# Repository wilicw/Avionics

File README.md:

# Avionics System

## Get Started

### [Install PlatformIO CLI](https://docs.platformio.org/en/latest/)

### Build Source Code

```
make
```

### Upload

```
make upload
```

## System Architecture

## [LICENSE](https://github.com/NCKU-ISP/Avionics/blob/main/LICENSE)

## Contact Us

To report any bugs or commit any new features, please create a new pull request and describe the issues in detail. If you are interested in our project and want to support us, please contact us with the following email: e94066157@gs.ncku.edu.tw, thanks!

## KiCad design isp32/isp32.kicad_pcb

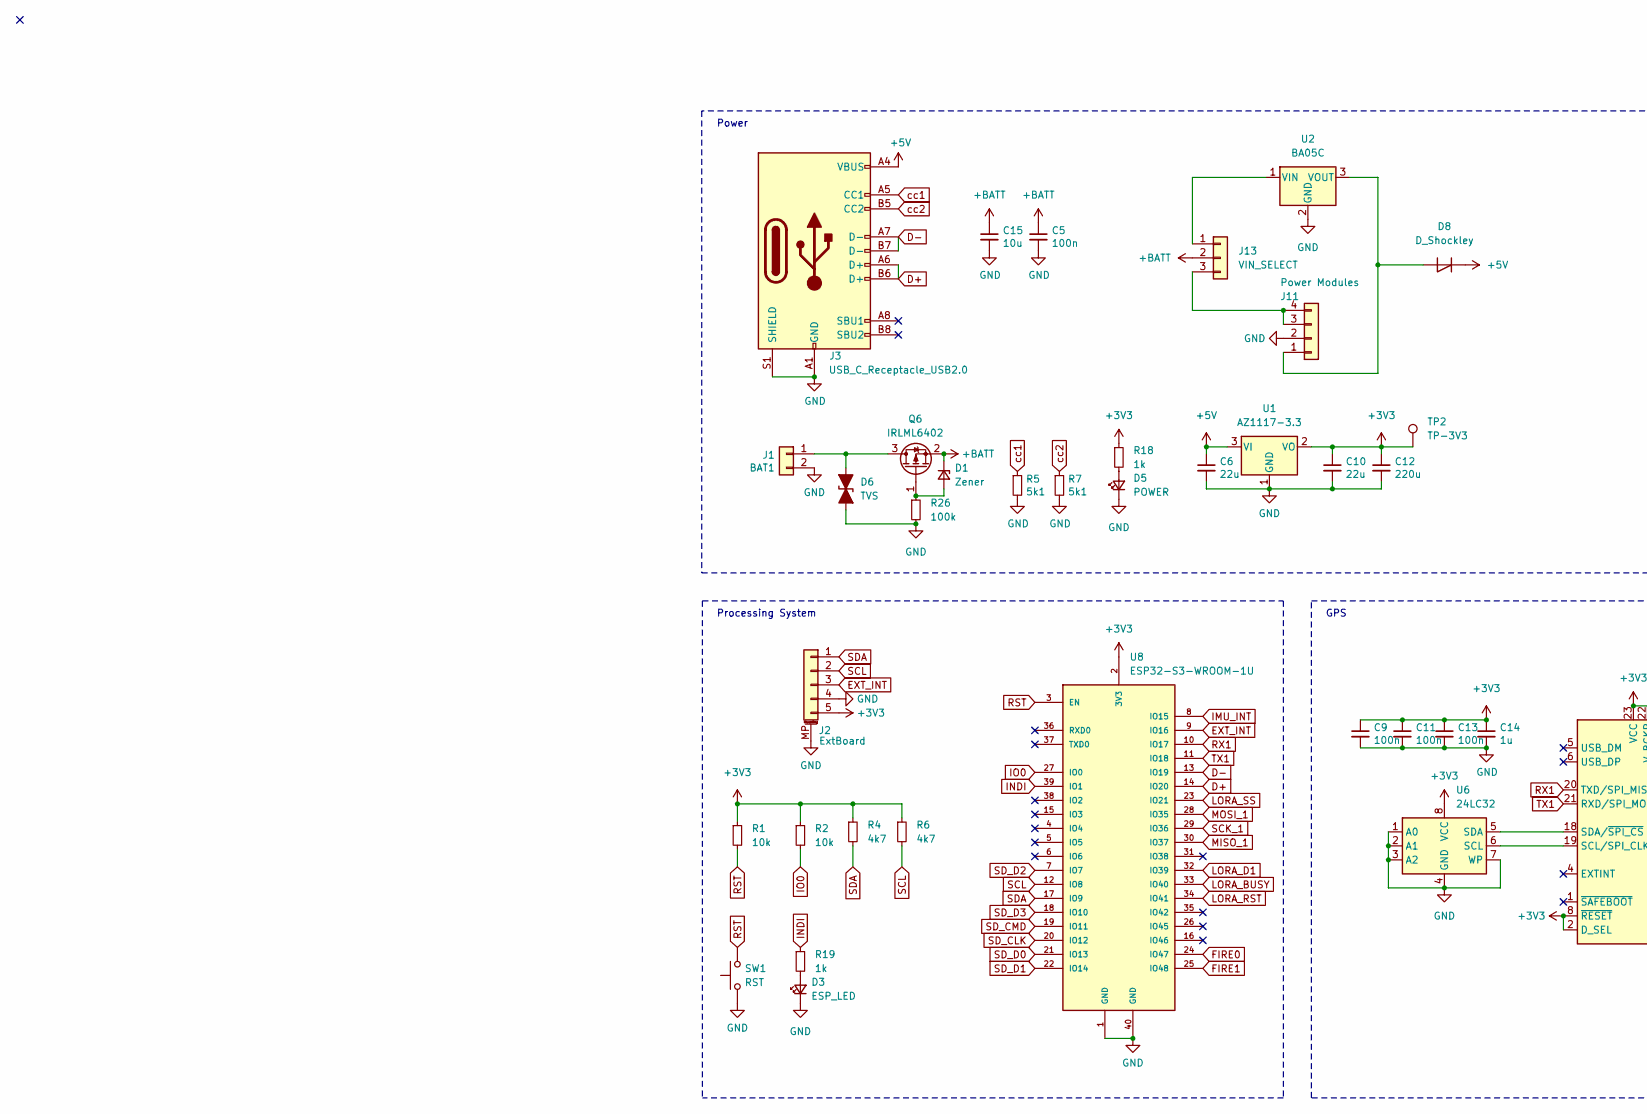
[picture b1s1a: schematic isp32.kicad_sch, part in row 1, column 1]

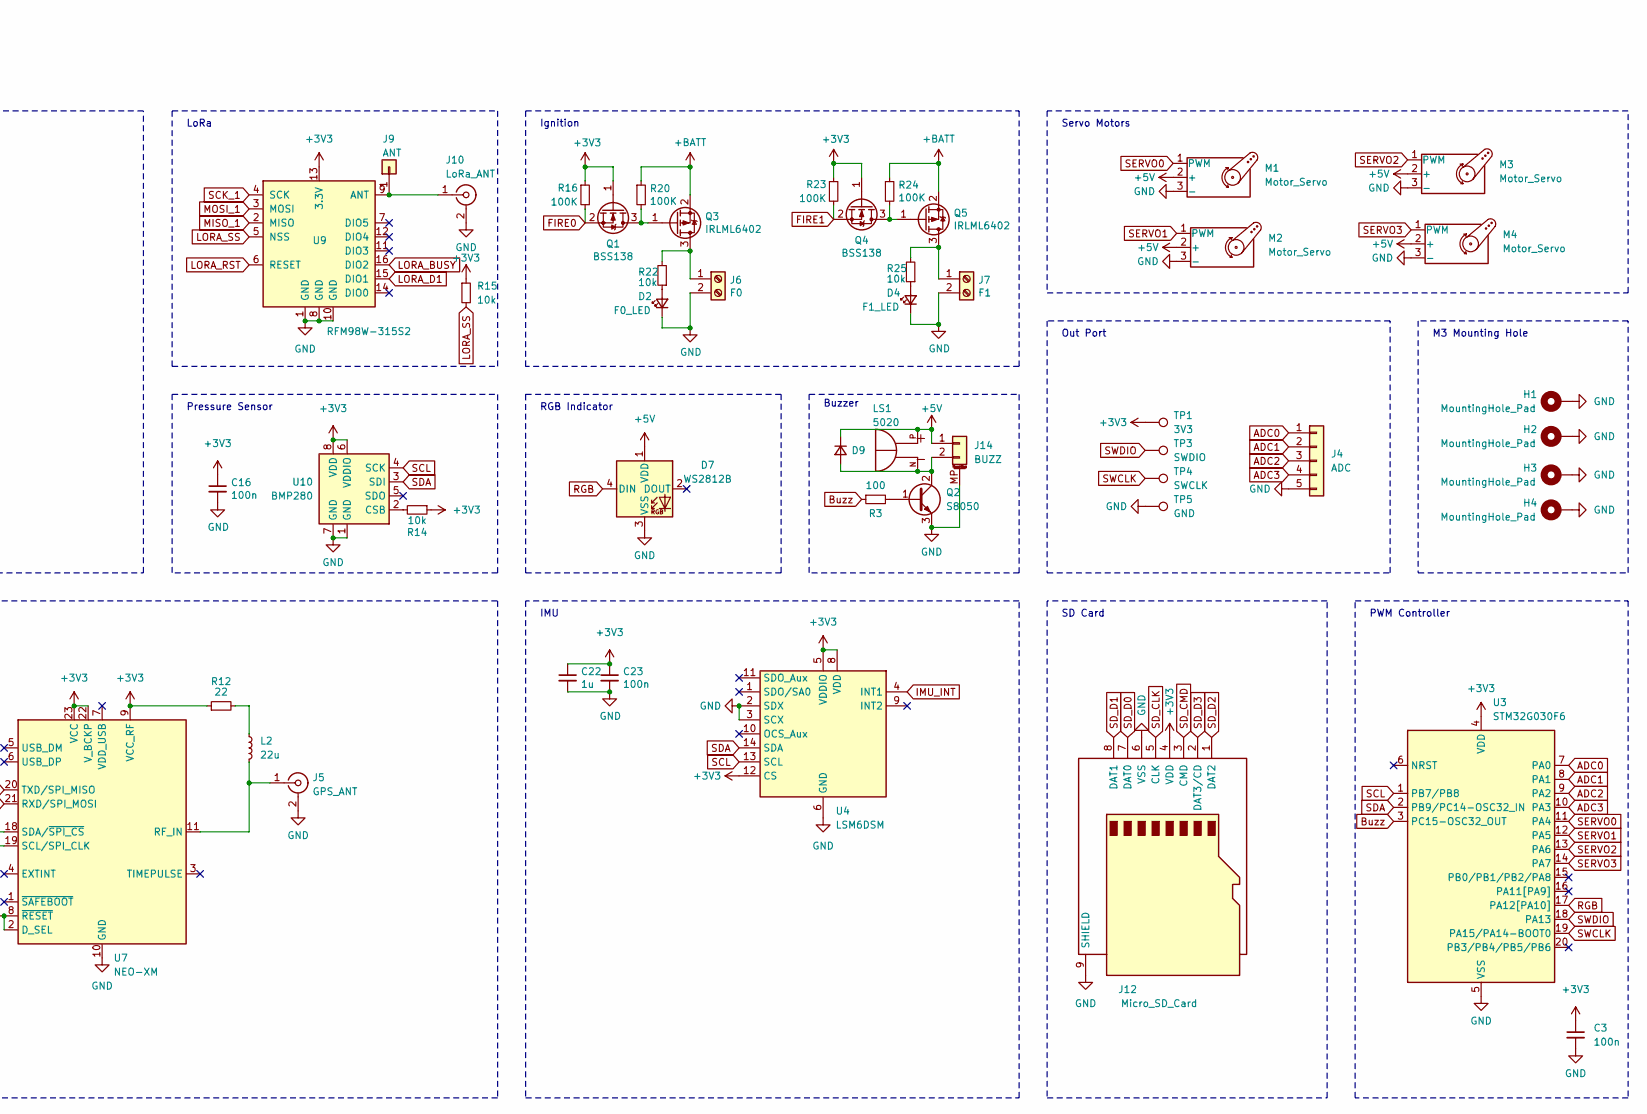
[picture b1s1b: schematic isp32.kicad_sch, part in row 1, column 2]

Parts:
C3, C9, C11, C13, C16, C23: 100n; C_0603_1608Metric
C5: 100n; C_0805_2012Metric
C6, C10: 22u; C_0603_1608Metric
C12: 220u; CP_EIA-3528-12_Kemet-T
C14, C22: 1u; C_0603_1608Metric
C15: 10u; C_0805_2012Metric
D1: Zener; D_SOD-123
D2: F0_LED; LED_0603_1608Metric
D3: ESP_LED; LED_0603_1608Metric
D4: F1_LED; LED_0603_1608Metric
D5: POWER; LED_0603_1608Metric
D6: TVS; D_SMB
D7: WS2812B; LED_WS2812B_PLCC4_5.0x5.0mm_P3.2mm
D8: D_Shockley; D_SOD-123
D9: D_Small; D_SOD-123
H1, H2, H3, H4: MountingHole_Pad; MountingHole_3.2mm_M3_ISO7380_Pad
J1: BAT1; JST_XH_S2B-XH-A-1_1x02_P2.50mm_Horizontal
J2: ExtBoard; Molex_PicoBlade_53261-0571_1x05-1MP_P1.25mm_Horizontal
J3: USB_C_Receptacle_USB2.0; USB_C_Receptacle_Palconn_UTC16-G
J4: ADC; PinHeader_1x05_P1.27mm_Vertical
J5: GPS_ANT; U.FL_Hirose_U.FL-R-SMT-1_Vertical
J6: F0; TerminalBlock_Phoenix_MPT-0,5-2-2.54_1x02_P2.54mm_Horizontal
J7: F1; TerminalBlock_Phoenix_MPT-0,5-2-2.54_1x02_P2.54mm_Horizontal
J9: ANT; PinHeader_1x01_P2.00mm_Vertical
J10: LoRa_ANT; U.FL_Hirose_U.FL-R-SMT-1_Vertical
J11: Power Modules; PinSocket_1x04_P2.54mm_Vertical
J12: Micro_SD_Card; microSD_HC_Wuerth_693072010801
J13: VIN_SELECT; PinHeader_1x03_P2.54mm_Vertical
J14: BUZZ; Molex_PicoBlade_53261-0271_1x02-1MP_P1.25mm_Horizontal
L2: 22u; L_0805_2012Metric
LS1: 5020; XDCR_KSSG33J12-3; PARTREV 1.4
M1, M2, M3, M4: Motor_Servo; PinHeader_1x03_P2.54mm_Vertical
Q1, Q4: BSS138; SOT-23
Q2: S8050; SOT-23
Q3, Q5, Q6: IRLML6402; SOT-23
R1, R2, R14, R15, R22, R25: 10k; R_0603_1608Metric
R3: 100; R_0603_1608Metric
R4, R6: 4k7; R_0603_1608Metric
R5, R7: 5k1; R_0603_1608Metric
R12: 22; R_0603_1608Metric
R16, R20, R23, R24: 100K; R_0603_1608Metric
R18, R19: 1k; R_0603_1608Metric
R26: 100k; R_0603_1608Metric
SW1: RST; SW_SPST_FSMSM
TP1: 3V3; TestPoint_Pad_D1.0mm
TP2: TP-3V3; TestPoint_Pad_D1.0mm
TP3: SWDIO; TestPoint_Pad_D1.0mm
TP4: SWCLK; TestPoint_Pad_D1.0mm
TP5: GND; TestPoint_Pad_D1.0mm
U1: AZ1117-3.3; SOT-223-3_TabPin2
U2: BA05C; TO-252-2
U3: STM32G030F6; TSSOP-20_4.4x6.5mm_P0.65mm
U4: LSM6DSM; LGA-14_3x2.5mm_P0.5mm_LayoutBorder3x4y
U6: 24LC32; SOIC-8_3.9x4.9mm_P1.27mm
U7: NEO-XM; ublox_NEO
U8: ESP32-S3-WROOM-1U; XCVR_ESP32-S3-WROOM-1U; PARTREV v0.6
U9: RFM98W-315S2; HOPERF_RFM9XW_SMD
U10: BMP280; Bosch_LGA-8_2x2.5mm_P0.65mm_ClockwisePinNumbering

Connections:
+3V3: C3.1, C9.1, C10.1, C11.1, C12.1, C13.1, C14.1, C16.1, C22.1, C23.1, J2.5, J12.4 (VDD), Q1.1 (G), Q4.1 (G), R1.1, R2.1, R4.1, R6.1, R12.1, R14.1, R15.1, R16.1, R18.1, R23.1, TP1.1, TP2.1, U1.2 (VO), U3.4 (VDD), U4.5 (VDDIO), U4.8 (VDD), U4.12 (CS), U6.8 (VCC), U7.2 (D_SEL), U7.8 (~RESET), U7.9 (VCC_RF), U7.22 (V_BCKP), U7.23 (VCC), U8.2 (3V3), U9.13 (3.3V), U10.6 (VDDIO), U10.8 (VDD)
+5V: C6.1, D7.1 (VDD), D8.1 (K), D9.1 (K), J3.A4 (VBUS), J3.A9 (VBUS), J3.B4 (VBUS), J3.B9 (VBUS), J14.1, LS1.P, M1.2 (+), M2.2 (+), M3.2 (+), M4.2 (+), U1.3 (VI)
+BATT: C5.1, C15.1, D1.1 (K), J13.2, Q3.2 (S), Q5.2 (S), Q6.2 (S), R20.1, R24.1
ADC0: J4.1, U3.7 (PA0)
ADC1: J4.2, U3.8 (PA1)
ADC2: J4.3, U3.9 (PA2)
ADC3: J4.4, U3.10 (PA3)
Buzz: R3.1, U3.3 (PC15-OSC32_OUT)
D+: J3.A6 (D+), J3.B6 (D+), U8.14 (IO20)
D-: J3.A7 (D-), J3.B7 (D-), U8.13 (IO19)
EXT_INT: J2.3, U8.9 (IO16)
FIRE0: Q1.2 (S), R16.2, U8.24 (IO47)
FIRE1: Q4.2 (S), R23.2, U8.25 (IO48)
GND: C3.2, C5.2, C6.2, C9.2, C10.2, C11.2, C12.2, C13.2, C14.2, C15.2, C16.2, C22.2, C23.2, D2.1 (K), D3.1 (K), D4.1 (K), D5.1 (K), D6.1 (A1), D7.3 (VSS), H1.1, H2.1, H3.1, H4.1, J1.2, J2.4, J2.MP (MountPin), J3.A1 (GND), J3.A12 (GND), J3.B1 (GND), J3.B12 (GND), J3.S1 (SHIELD), J4.5, J5.2 (Ext), J6.2, J7.2, J10.2 (Ext), J11.2, J12.6 (VSS), J12.9 (SHIELD), J14.MP (MountPin), M1.3 (-), M2.3 (-), M3.3 (-), M4.3 (-), Q2.3 (E), R5.2, R7.2, R26.2, SW1.1, TP5.1, U1.1 (GND), U2.2 (GND), U3.5 (VSS), U4.2 (SDX), U4.3 (SCX), U4.6 (GND), U4.7 (GND), U6.1 (A0), U6.2 (A1), U6.3 (A2), U6.4 (GND), U6.7 (WP), U7.10 (GND), U7.12 (GND), U7.13 (GND), U7.24 (GND), U8.1 (GND), U8.40 (GND), U8.41_1 (GND), U8.41_2 (GND), U8.41_3 (GND), U8.41_4 (GND), U8.41_5 (GND), U8.41_6 (GND), U8.41_7 (GND), U8.41_8 (GND), U8.41_9 (GND), U9.1 (GND), U9.8 (GND), U9.10 (GND), U10.1 (GND), U10.7 (GND)
IMU_INT: U4.4 (INT1), U8.8 (IO15)
INDI: R19.1, U8.39 (IO1)
IO0: R2.2, U8.27 (IO0)
LORA_BUSY: U8.33 (IO40), U9.16 (DIO2)
LORA_D1: U8.32 (IO39), U9.15 (DIO1)
LORA_RST: U8.34 (IO41), U9.6 (RESET)
LORA_SS: R15.2, U8.23 (IO21), U9.5 (NSS)
MISO_1: U8.30 (IO37), U9.2 (MISO)
MOSI_1: U8.28 (IO35), U9.3 (MOSI)
unnamed: D1.2 (A), Q6.1 (G), R26.1
unnamed: D2.2 (A), R22.1
unnamed: D3.2 (A), R19.2
unnamed: D4.2 (A), R25.1
unnamed: D5.2 (A), R18.2
unnamed: D6.2 (A2), J1.1, Q6.3 (D)
unnamed: D8.2 (A), J11.1, U2.3 (VOUT)
unnamed: D9.2 (A), J14.2, LS1.N, Q2.2 (C)
unnamed: J5.1 (In), L2.2, U7.11 (RF_IN)
unnamed: J6.1, Q3.3 (D), R22.2
unnamed: J7.1, Q5.3 (D), R25.2
unnamed: J9.1, J10.1 (In), U9.9 (ANT)
unnamed: J11.3, J11.4, J13.3
unnamed: J13.1, U2.1 (VIN)
unnamed: L2.1, R12.2
unnamed: Q1.3 (D), Q3.1 (G), R20.2
unnamed: Q2.1 (B), R3.2
unnamed: Q4.3 (D), Q5.1 (G), R24.2
unnamed: U6.6 (SCL), U7.19 (SCL/SPI_CLK)
unnamed: U6.5 (SDA), U7.18 (SDA/~SPI_CS)
unnamed: R14.2, U10.2 (CSB)
RGB: D7.4 (DIN), U3.17 (PA12[PA10])
RST: R1.2, SW1.2, U8.3 (EN)
RX1: U7.20 (TXD/SPI_MISO), U8.10 (IO17)
SCK_1: U8.29 (IO36), U9.4 (SCK)
SCL: J2.2, R6.2, U3.1 (PB7/PB8), U4.13 (SCL), U8.12 (IO8), U10.4 (SCK)
SDA: J2.1, R4.2, U3.2 (PB9/PC14-OSC32_IN), U4.14 (SDA), U8.17 (IO9), U10.3 (SDI)
SD_CLK: J12.5 (CLK), U8.20 (IO12)
SD_CMD: J12.3 (CMD), U8.19 (IO11)
SD_D0: J12.7 (DAT0), U8.21 (IO13)
SD_D1: J12.8 (DAT1), U8.22 (IO14)
SD_D2: J12.1 (DAT2), U8.7 (IO7)
SD_D3: J12.2 (DAT3/CD), U8.18 (IO10)
SERVO0: M1.1 (PWM), U3.11 (PA4)
SERVO1: M2.1 (PWM), U3.12 (PA5)
SERVO2: M3.1 (PWM), U3.13 (PA6)
SERVO3: M4.1 (PWM), U3.14 (PA7)
SWCLK: TP4.1, U3.19 (PA15/PA14-BOOT0)
SWDIO: TP3.1, U3.18 (PA13)
TX1: U7.21 (RXD/SPI_MOSI), U8.11 (IO18)
cc1: J3.A5 (CC1), R5.1
cc2: J3.B5 (CC2), R7.1

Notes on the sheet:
IMU
PWM Controller
Ignition
M3 Mounting Hole
Servo Motors
RGB Indicator
Out Port
Buzzer
Processing System
Pressure Sensor
LoRa
GPS
SD Card
Power

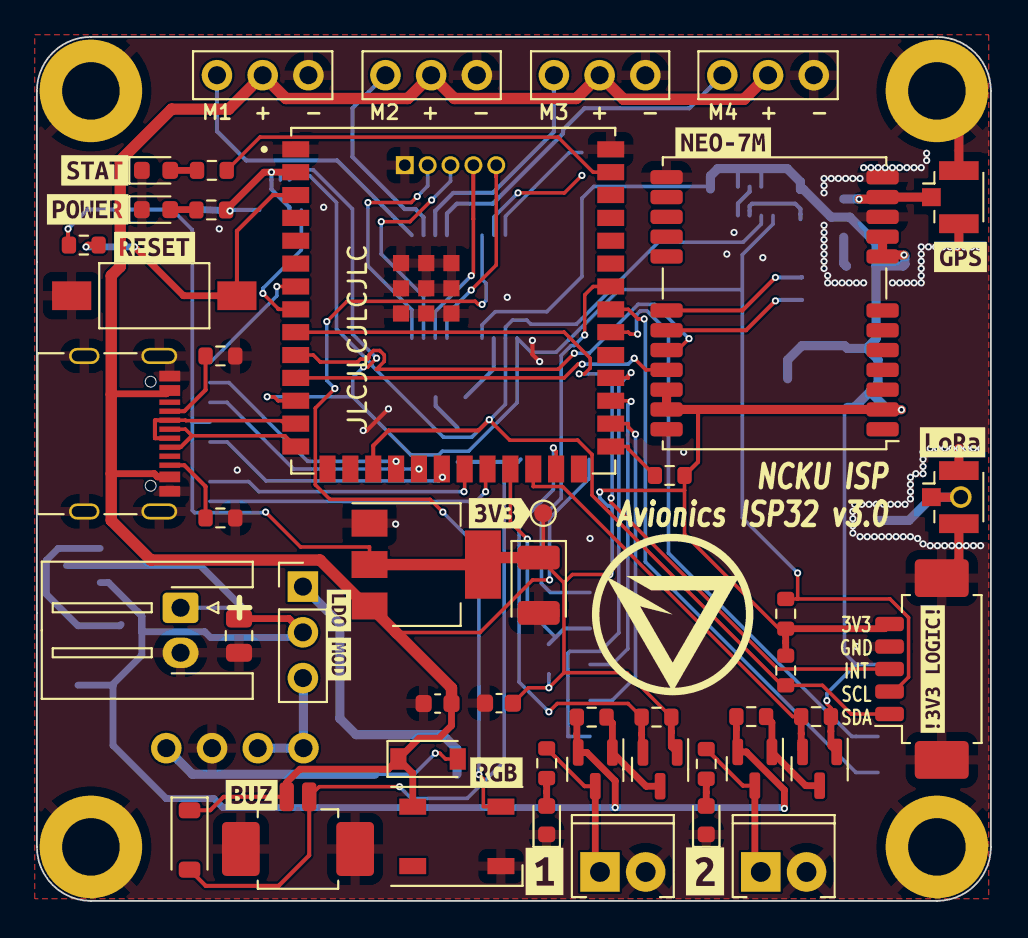
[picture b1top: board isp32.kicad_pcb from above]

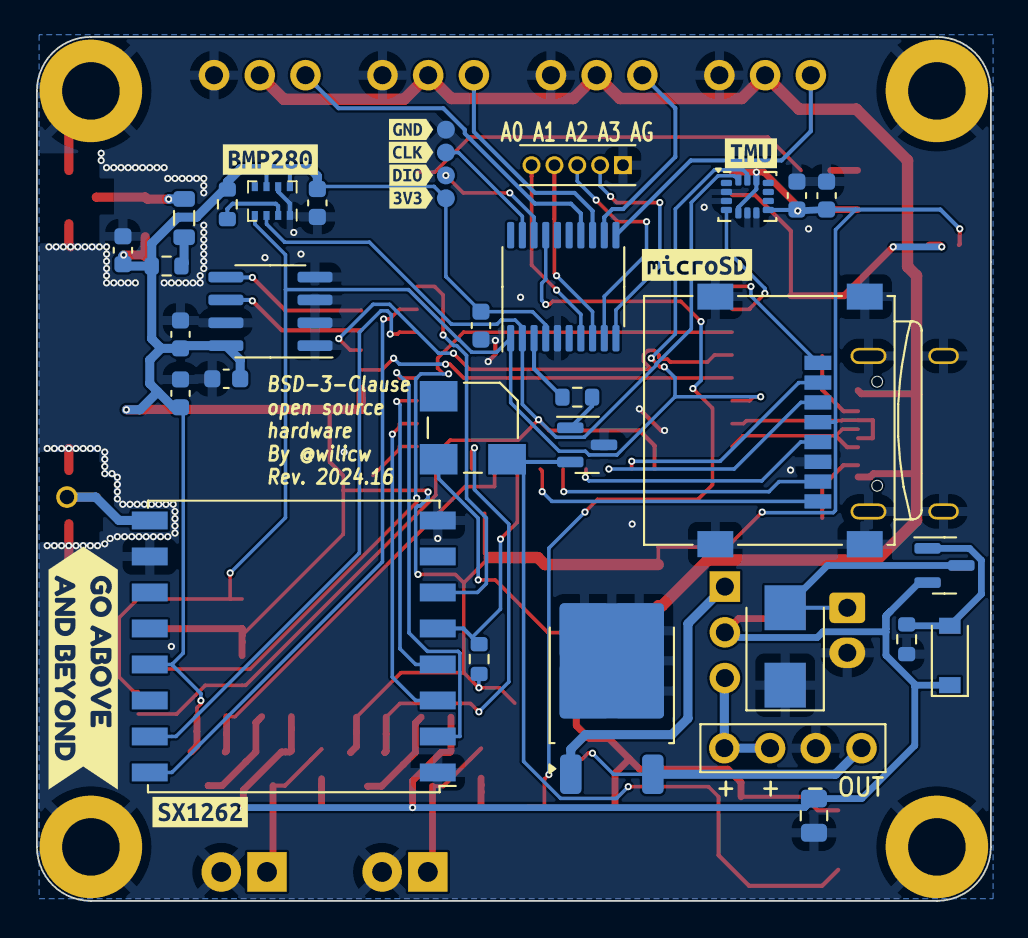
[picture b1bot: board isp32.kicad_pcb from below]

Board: 2 copper layers, 53.0 x 48.0 mm, 108 parts (43 on the bottom side), 65 nets.

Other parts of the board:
kibuzzard-63CD1E7F: G***; kibuzzard-63CD1E7F
kibuzzard-63CD1E61: G***; kibuzzard-63CD1E61
kibuzzard-63CD1EC0: G***; kibuzzard-63CD1EC0
kibuzzard-63CD1EC5: G***; kibuzzard-63CD1EC5
kibuzzard-63CD04EB: G***; kibuzzard-63CD04EB
kibuzzard-63CD04FB: G***; kibuzzard-63CD04FB
kibuzzard-641A73AC: G***; kibuzzard-641A73AC
kibuzzard-641A73E5: G***; kibuzzard-641A73E5
kibuzzard-641A73FA: G***; kibuzzard-641A73FA
kibuzzard-641A737F: G***; kibuzzard-641A737F
kibuzzard-641A7395: G***; kibuzzard-641A7395
kibuzzard-641A7704: G***; kibuzzard-641A7704
kibuzzard-642D97EE: G***; kibuzzard-642D97EE
kibuzzard-661FABB5: G***; kibuzzard-661FABB5
kibuzzard-661FAECF: G***; kibuzzard-661FAECF
kibuzzard-661FBC0A: G***; kibuzzard-661FBC0A
kibuzzard-661FBC21: G***; kibuzzard-661FBC21
kibuzzard-66439A83: G***; kibuzzard-66439A83
kibuzzard-66439ACD: G***; kibuzzard-66439ACD
kibuzzard-66439AF0: G***; kibuzzard-66439AF0
kibuzzard-66439B8F: G***; kibuzzard-66439B8F
kibuzzard-66439B33: G***; kibuzzard-66439B33
kibuzzard-66439C31: G***; kibuzzard-66439C31
